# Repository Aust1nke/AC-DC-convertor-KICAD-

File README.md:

# these files are simply kicad files, showing my project for the AC-DC convertor

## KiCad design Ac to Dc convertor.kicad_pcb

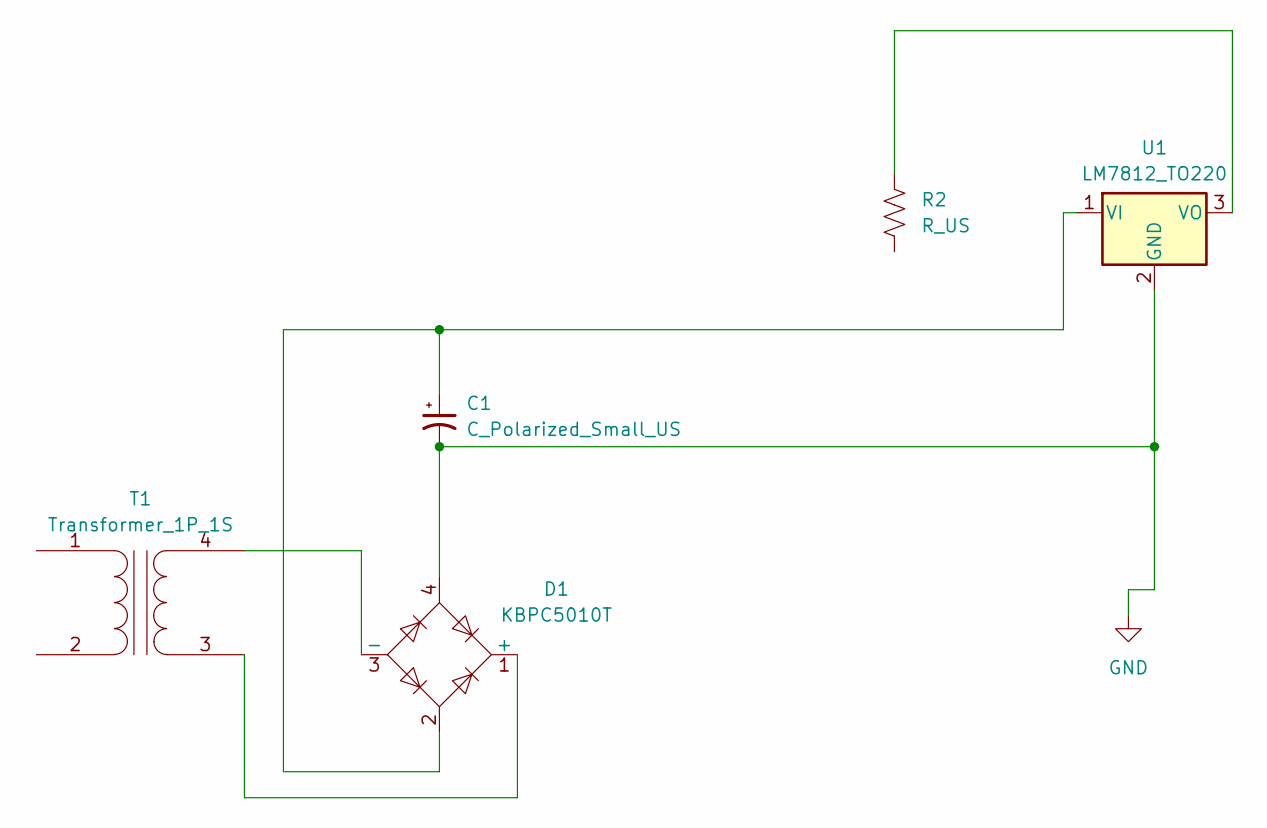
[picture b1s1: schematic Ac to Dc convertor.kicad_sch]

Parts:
C1: C_Polarized_Small_US; C_0201_0603Metric
D1: KBPC5010T; Diode_Bridge_Round_D9.8mm
R2: R_US; R_0201_0603Metric
T1: Transformer_1P_1S; Transformer_CurrentSense_8.4x7.2mm
U1: LM7812_TO220; TO-220-3_Vertical

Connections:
GND: C1.2, D1.4, U1.2 (GND)
unnamed: D1.1 (+), T1.3 (SA)
unnamed: D1.3 (-), T1.4 (SB)
unnamed: C1.1, D1.2, U1.1 (VI)
unnamed: R2.1, U1.3 (VO)

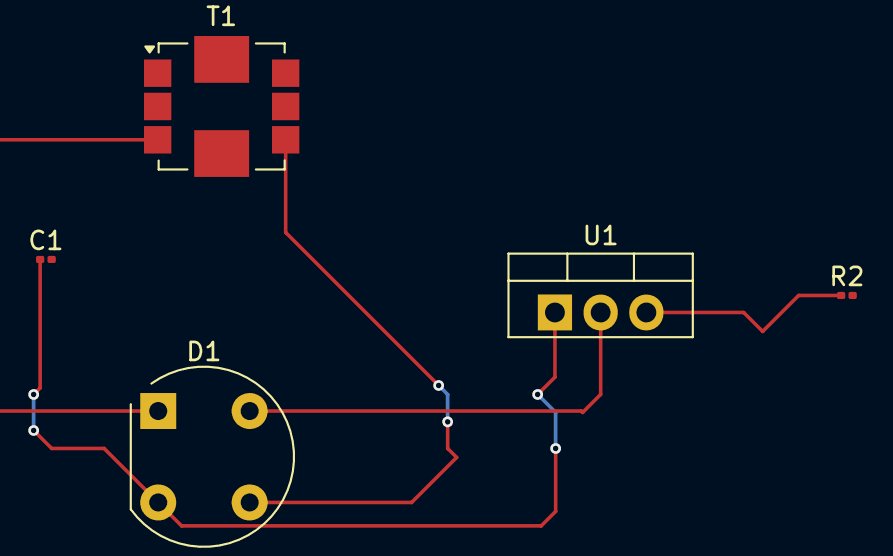
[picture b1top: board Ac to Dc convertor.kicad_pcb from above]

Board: 2 copper layers, 5 parts (0 on the bottom side), 5 nets.

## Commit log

2024-12-05 Add files via upload
    These are kicad files for my small project that I was doing ,.. an AC to DC convertor
